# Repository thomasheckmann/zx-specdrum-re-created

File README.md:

# zx-specdrum-re-created
Recreated and improved version of [Currah SpecDrum](https://spectrumcomputing.co.uk/entry/1000062/Hardware/Cheetah_SpecDrum) Interface for ZX Spectrum

Work on this was initiated because existing schema found on the internet is with errors.

# Version 1
First version is more or less a 1:1 copy of the original interface. With help I got the correct values and type for all the Capacitors. Thanks to Matthew Logue for providing the information from his original interfaces, helping out with how to use the old software as well as doing a test build of the interface.

The only changes compared with original:
* PCB made more compact to fit into my ZX-Bus-Extender board, you can use a normal edge connecter if you prefer.
* Some components moved, all ICs now have the same orientation.
* Make sure all ICs have decoupling capacitors.
* Added a 3.5" mini-jack plug for audio out.

BOM:

## This is how version 1 turned out
| <!---> | <!---> |
| ------ | ------ |
|||

And it sounds like this in action https://youtube.com/shorts/cKAM5VnGr6U?feature=share

# Version 2
This update fixes a few errors from the initial release and introduces an option for sound enhancement:

* bypassed the anti-aliasing filter and somewhat improved the bass response
* option to switch between original or improved output (using jumper)
* C7 - changed from Ceramic 1uF to Electrolytic 10uF

BOM (recommended order):
* 4 x 6,2K Resistor
* 2 x 10,0K Resistor
* 2 x 100K Resistor
* 1 x 390R Resistor
* 1 x 680R Resistor
* 1 x 390K Resistor

* 3 x 100nF - MLC Capacitor P2,54
* 1 x 1nF - Ceramic Capacitor P2,54

* 1 x 2,7nF - Ceramic Capacitor P2,54
* 1 x 2,2nF - Ceramic Capacitor P2,54
* 1 x 82pF - Ceramic NPO P5,08

* 3 x 1uF - Tantal P5,08
* 1 x 22uF - Electrolyte Capacitor P2,54
* 1 x 10uF - Electrolyte Capacitor P2,54

* 1 x 74LS32
* 1 x TL084
* 1 x ZN428E-8
* 3.5 mono jack [like this](https://elektronik-lavpris.dk/p136328/pj-211-35mm-mono-jack-chassis-med-afbryder-switch/)

The sound improvement modification was suggested by D.A. Wilson of Hideaway Studio and is used here with permission. You can read about the mod [here](https://spectrumcomputing.co.uk/forums/viewtopic.php?t=4845)

## Version v1.2
[Hear the interface](https://youtube.com/shorts/OHfJIYJJYTI) in action here, playing a demo from the original [software](https://spectrumcomputing.co.uk/entry/8720/ZX-Spectrum/SpecDrum)

| <!---> | <!---> |
| ------ | ------ |
|||

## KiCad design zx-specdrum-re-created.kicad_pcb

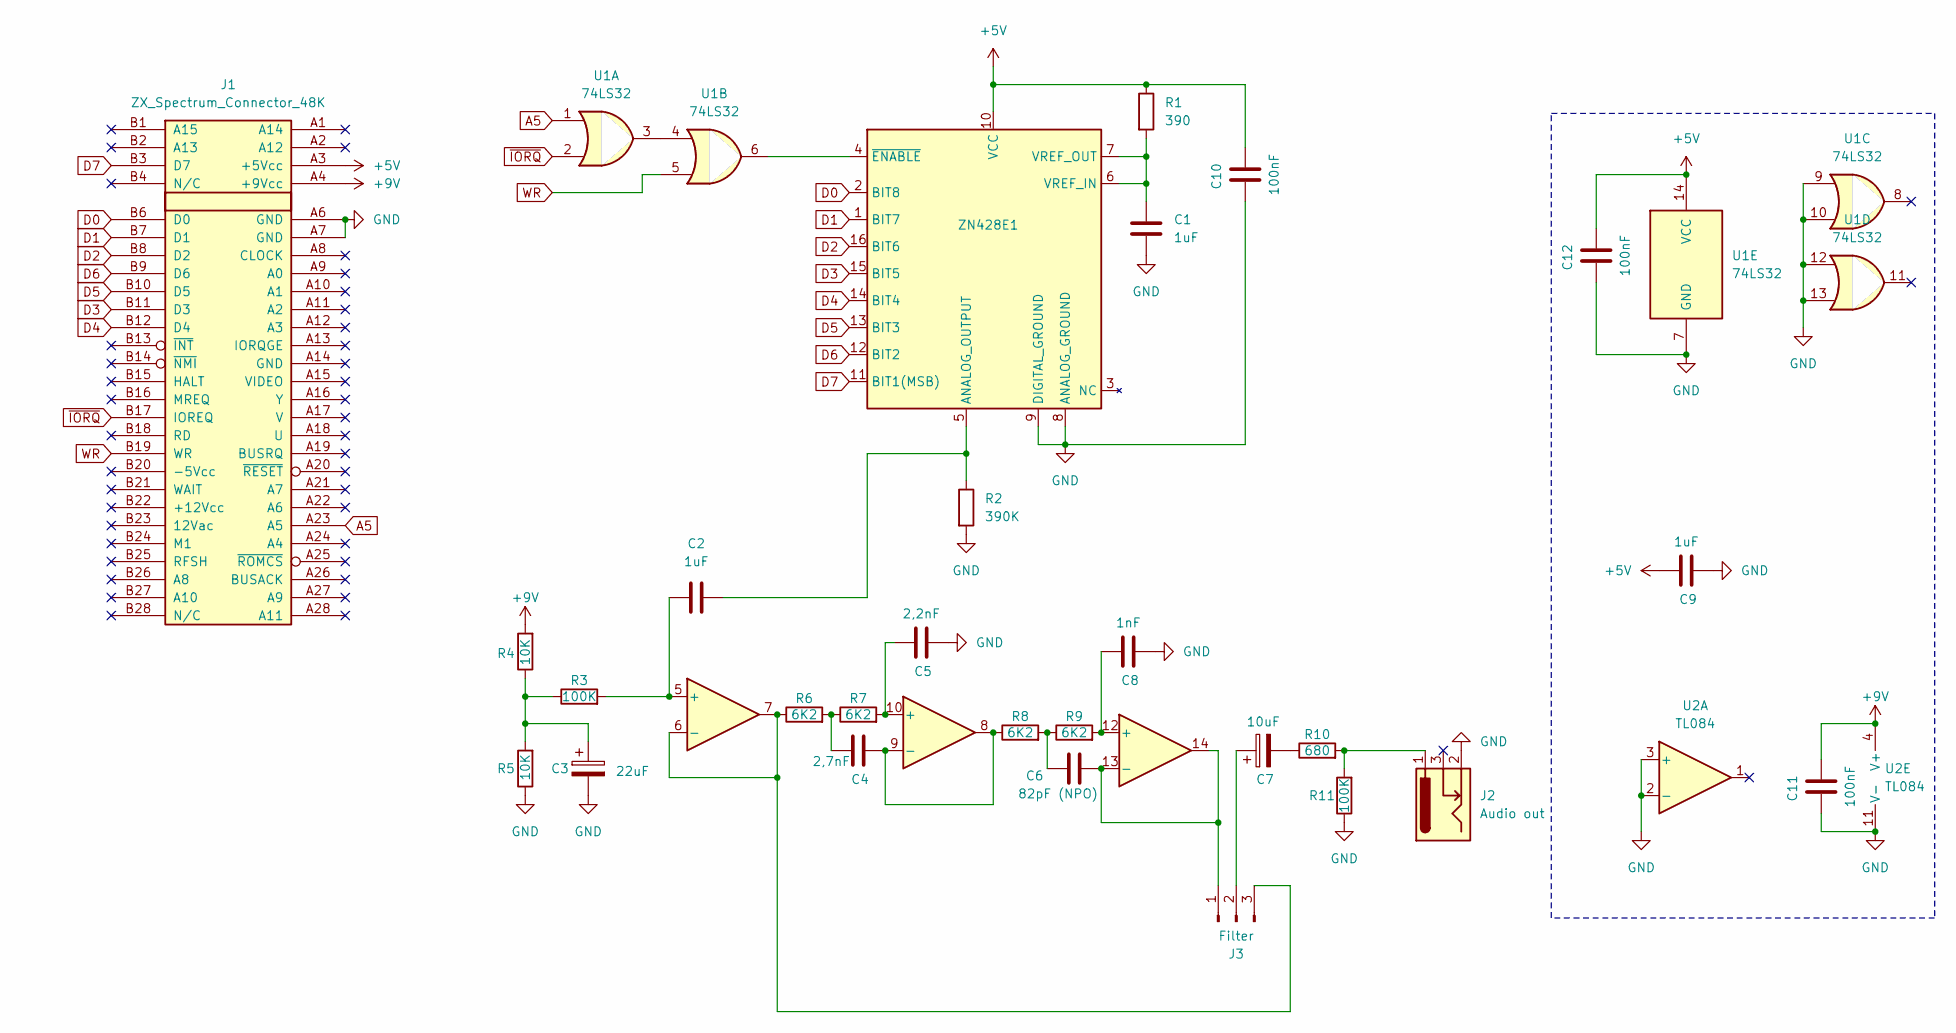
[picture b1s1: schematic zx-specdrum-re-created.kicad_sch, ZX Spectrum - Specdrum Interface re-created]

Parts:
C1, C2, C9: 1uF; C_Disc_D4.3mm_W1.9mm_P5.00mm
C3: 22uF; CP_Radial_D5.0mm_P2.50mm
C4: 2,7nF; C_Disc_D3.0mm_W1.6mm_P2.50mm
C5: 2,2nF; C_Disc_D3.0mm_W1.6mm_P2.50mm
C6: 82pF (NPO); C_Disc_D4.3mm_W1.9mm_P5.00mm
C7: 10uF; CP_Radial_D5.0mm_P2.50mm
C8: 1nF; C_Disc_D3.0mm_W1.6mm_P2.50mm
C10, C11, C12: 100nF; C_Disc_D3.0mm_W1.6mm_P2.50mm
J1: ZX_Spectrum_Connector_48K; EDGE_ZX_SPECTRUM
J2: Audio out; 3.5mm mono jack chassis with switch
J3: Filter; PinHeader_1x03_P2.54mm_Vertical
R1: 390; R_Axial_DIN0207_L6.3mm_D2.5mm_P10.16mm_Horizontal
R2: 390K; R_Axial_DIN0207_L6.3mm_D2.5mm_P10.16mm_Horizontal
R3, R11: 100K; R_Axial_DIN0207_L6.3mm_D2.5mm_P10.16mm_Horizontal
R4, R5: 10K; R_Axial_DIN0207_L6.3mm_D2.5mm_P10.16mm_Horizontal
R6, R7, R8, R9: 6K2; R_Axial_DIN0207_L6.3mm_D2.5mm_P10.16mm_Horizontal
R10: 680; R_Axial_DIN0207_L6.3mm_D2.5mm_P10.16mm_Horizontal
U1: 74LS32; DIP-14_W7.62mm_Socket
U2: TL084; DIP-14_W7.62mm_Socket
ZN428E1: DIP-16_W7.62mm_Socket

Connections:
+5V: C9.1, C10.1, C12.1, J1.A3 (+5Vcc), R1.1, U1.14 (VCC), ZN428E1.10 (VCC)
+9V: C11.1, J1.A4 (+9Vcc), R4.2, U2.4 (V+)
A5: J1.A23 (A5), U1.1
D0: J1.B6 (D0), ZN428E1.2 (BIT8)
D1: J1.B7 (D1), ZN428E1.1 (BIT7)
D2: J1.B8 (D2), ZN428E1.16 (BIT6)
D3: J1.B11 (D3), ZN428E1.15 (BIT5)
D4: J1.B12 (D4), ZN428E1.14 (BIT4)
D5: J1.B10 (D5), ZN428E1.13 (BIT3)
D6: J1.B9 (D6), ZN428E1.12 (BIT2)
D7: J1.B3 (D7), ZN428E1.11 (BIT1(MSB))
GND: C1.2, C3.2, C5.2, C8.2, C9.2, C10.2, C11.2, C12.2, J1.A6 (GND), J1.A7 (GND), J2.2, R2.2, R5.1, R11.1, U1.7 (GND), U1.9, U1.10, U1.12, U1.13, U2.2 (-), U2.3 (+), U2.11 (V-), ZN428E1.8 (ANALOG_GROUND), ZN428E1.9 (DIGITAL_GROUND)
unnamed: C3.1, R3.1, R4.1, R5.2
unnamed: C4.1, R6.2, R7.1
unnamed: C6.1, R8.2, R9.1
unnamed: C7.2, R10.1
unnamed: J2.1, R10.2, R11.2
unnamed: C6.2, J3.1, U2.13 (-), U2.14
unnamed: C7.1, J3.2
unnamed: J3.3, R6.1, U2.6 (-), U2.7
unnamed: U1.3, U1.4
unnamed: C2.1, R3.2, U2.5 (+)
unnamed: C5.1, R7.2, U2.10 (+)
unnamed: C4.2, R8.1, U2.8, U2.9 (-)
unnamed: C8.1, R9.2, U2.12 (+)
unnamed: C2.2, R2.1, ZN428E1.5 (ANALOG_OUTPUT)
unnamed: C1.1, R1.2, ZN428E1.6 (VREF_IN), ZN428E1.7 (VREF_OUT)
unnamed: U1.6, ZN428E1.4 (~ENABLE)
WR: J1.B19 (WR), U1.5
~IORQ: J1.B17 (IOREQ), U1.2

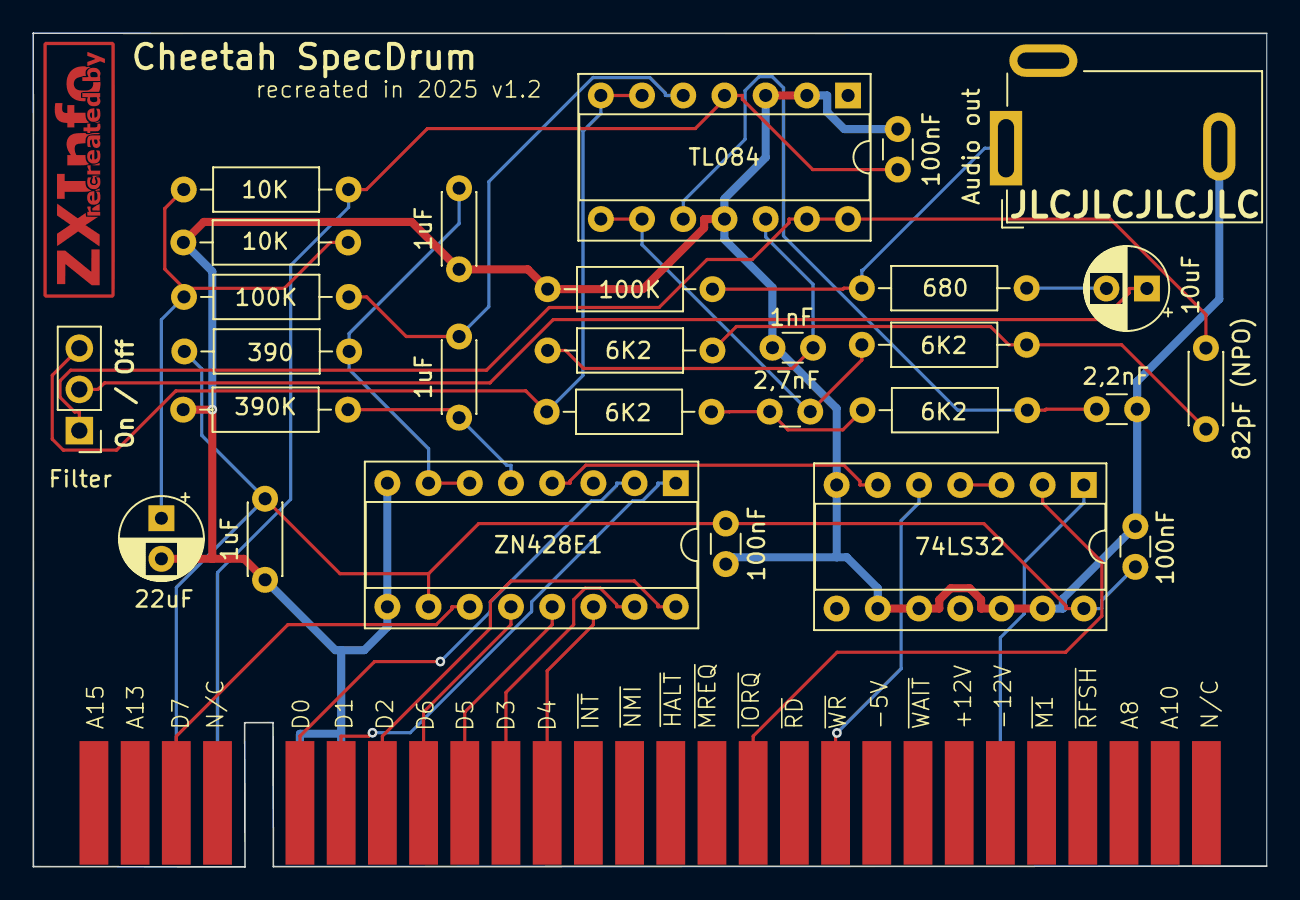
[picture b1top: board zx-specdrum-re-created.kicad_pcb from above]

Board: 2 copper layers, 76.0 x 51.4 mm, 30 parts (0 on the bottom side), 30 nets.

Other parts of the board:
G200: LOGO; ZXInfo_kicad_logo_copper_16.5x5

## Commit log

2025-02-27 Intial version
2025-02-27 Added v1.1
2025-02-27 small update
2025-02-27 Version 1.2 update
2025-02-28 Update README.md
    updated with v2
2025-03-14 v1.2
